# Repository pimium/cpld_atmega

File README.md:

# CPLD ATmega

An EDA Development Board to work with CPLD and ATmega

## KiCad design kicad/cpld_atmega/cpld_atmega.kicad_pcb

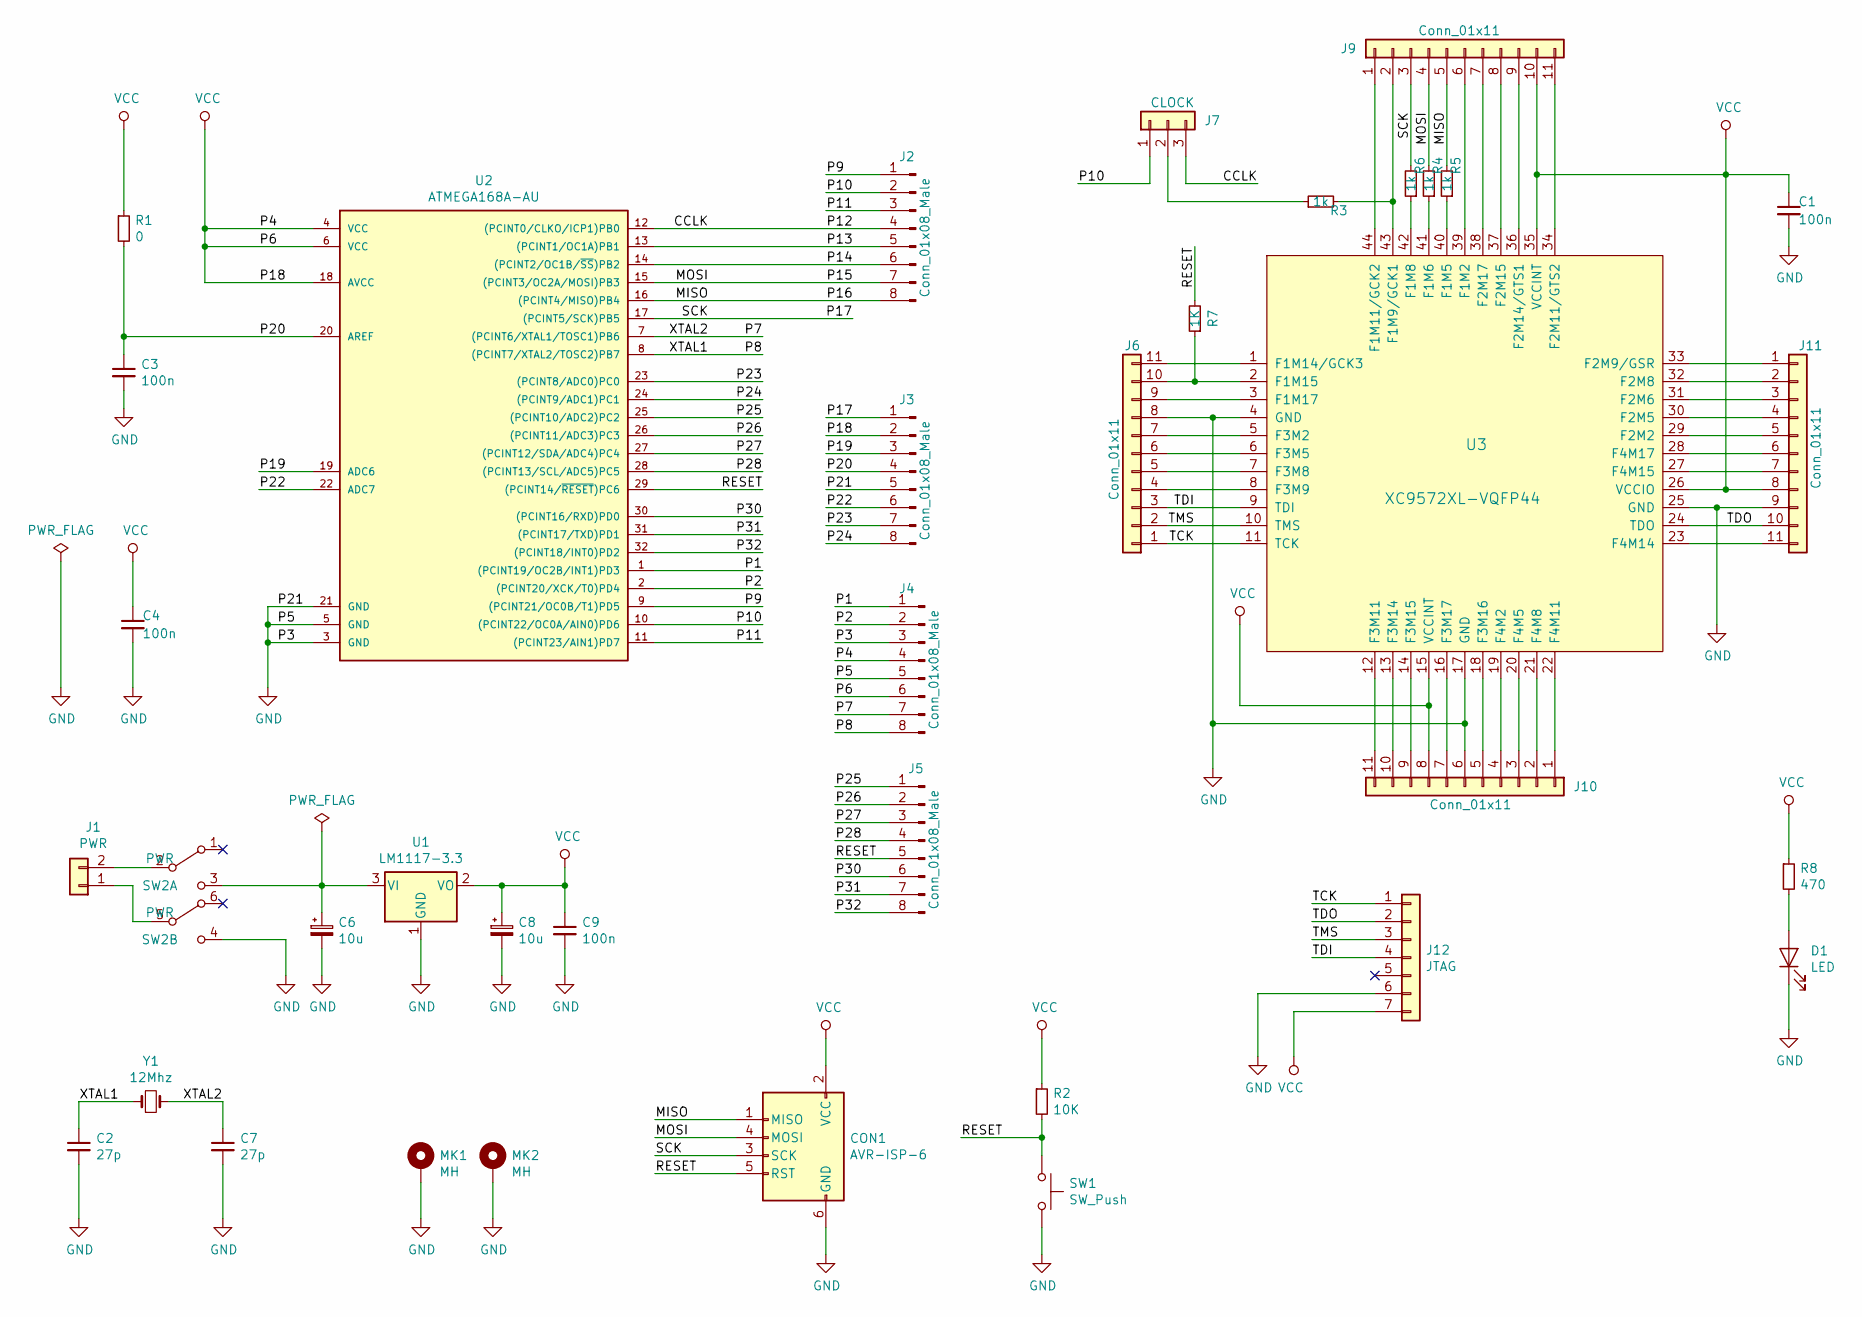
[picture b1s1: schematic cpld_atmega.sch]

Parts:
C1: 100n; C_0805_HandSoldering
C2, C7: 27p; C_0805_HandSoldering
C3, C4, C9: 100n; C_0805_2012Metric_Pad1.15x1.40mm_HandSolder
C6, C8: 10u; CP_Radial_D5.0mm_P2.50mm
CON1: AVR-ISP-6; Pin_Header_Straight_2x03_Pitch2.54mm
D1: LED; LED_1206_3216Metric_Pad1.42x1.75mm_HandSolder
J1: PWR; TerminalBlock_RND_205-00001_1x02_P5.00mm_Horizontal
J2, J3, J4, J5: Conn_01x08_Male; PinSocket_1x08_P2.54mm_Vertical
J6, J9, J10, J11: Conn_01x11; PinSocket_1x11_P2.54mm_Vertical
J7: CLOCK; PinSocket_1x03_P2.54mm_Vertical
J12: JTAG; PinSocket_1x07_P2.54mm_Vertical
MK1, MK2: MH; MountingHole_2.5mm_Pad
R1: 0; R_0805_2012Metric_Pad1.15x1.40mm_HandSolder
R2: 10K; R_0603_1608Metric_Pad1.05x0.95mm_HandSolder
R3, R4, R5, R6: 1k; R_0603_1608Metric_Pad1.05x0.95mm_HandSolder
R7: 1K; R_0603_1608Metric_Pad1.05x0.95mm_HandSolder
R8: 470; R_0603_1608Metric_Pad1.05x0.95mm_HandSolder
SW1: SW_Push; SW_PUSH_6mm
SW2: PWR; DPDT_WIDE_54_54
U1: LM1117-3.3; SOT-223-3_TabPin2
U2: ATMEGA168A-AU; TQFP-32_7x7mm_Pitch0.8mm
U3: XC9572XL-VQFP44; LQFP-44_10x10mm_P0.8mm
Y1: 12Mhz; Crystal_SMD_HC49-SD

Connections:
/CCLK: J2.4, J7.3, U2.12 ((PCINT0/CLKO/ICP1)PB0)
/MISO: CON1.1 (MISO), J2.8, J9.5, R5.2, U2.16 ((PCINT4/MISO)PB4)
/MOSI: CON1.4 (MOSI), J2.7, J9.4, R4.2, U2.15 ((PCINT3/OC2A/MOSI)PB3)
/P1: J4.1, U2.1 ((PCINT19/OC2B/INT1)PD3)
/P2: J4.2, U2.2 ((PCINT20/XCK/T0)PD4)
/P7: C7.1, J4.7, U2.7 ((PCINT6/XTAL1/TOSC1)PB6), Y1.2
/P8: C2.1, J4.8, U2.8 ((PCINT7/XTAL2/TOSC2)PB7), Y1.1
/P9: J2.1, U2.9 ((PCINT21/OC0B/T1)PD5)
/P10: J2.2, J7.1, U2.10 ((PCINT22/OC0A/AIN0)PD6)
/P11: J2.3, U2.11 ((PCINT23/AIN1)PD7)
/P13: J2.5, U2.13 ((PCINT1/OC1A)PB1)
/P14: J2.6, U2.14 ((PCINT2/OC1B/~SS~)PB2)
/P17: CON1.3 (SCK), J3.1, J9.3, R6.2, U2.17 ((PCINT5/SCK)PB5)
/P19: J3.3, U2.19 (ADC6)
/P20: C3.1, J3.4, R1.2, U2.20 (AREF)
/P22: J3.6, U2.22 (ADC7)
/P23: J3.7, U2.23 ((PCINT8/ADC0)PC0)
/P24: J3.8, U2.24 ((PCINT9/ADC1)PC1)
/P25: J5.1, U2.25 ((PCINT10/ADC2)PC2)
/P26: J5.2, U2.26 ((PCINT11/ADC3)PC3)
/P27: J5.3, U2.27 ((PCINT12/SDA/ADC4)PC4)
/P28: J5.4, U2.28 ((PCINT13/SCL/ADC5)PC5)
/P30: J5.6, U2.30 ((PCINT16/RXD)PD0)
/P31: J5.7, U2.31 ((PCINT17/TXD)PD1)
/P32: J5.8, U2.32 ((PCINT18/INT0)PD2)
/RESET: CON1.5 (RST), J5.5, R2.2, R7.2, SW1.1, U2.29 ((PCINT14/~RESET~)PC6)
/TCK: J6.1, J12.1, U3.11 (TCK)
/TDI: J6.3, J12.4, U3.9 (TDI)
/TDO: J11.10, J12.2, U3.24 (TDO)
/TMS: J6.2, J12.3, U3.10 (TMS)
GND: C1.2, C2.2, C3.2, C4.2, C6.2, C7.2, C8.2, C9.2, CON1.6 (GND), D1.1 (K), J3.5, J4.3, J4.5, J6.8, J10.6, J11.9, J12.6, MK1.1, MK2.1, SW1.2, SW2.4 (C), U1.1 (GND), U2.3 (GND), U2.5 (GND), U2.21 (GND), U3.4 (GND), U3.17 (GND), U3.25 (GND)
unnamed: C6.1, SW2.3 (C), U1.3 (VI)
unnamed: D1.2 (A), R8.2
unnamed: J1.1, SW2.5 (B)
unnamed: J1.2, SW2.2 (B)
unnamed: J6.4, U3.8 (F3M9)
unnamed: J6.5, U3.7 (F3M8)
unnamed: J6.6, U3.6 (F3M5)
unnamed: J6.7, U3.5 (F3M2)
unnamed: J6.9, U3.3 (F1M17)
unnamed: J6.10, R7.1, U3.2 (F1M15)
unnamed: J6.11, U3.1 (F1M14/GCK3)
unnamed: J7.2, R3.1
unnamed: J9.1, U3.44 (F1M11/GCK2)
unnamed: J9.2, R3.2, U3.43 (F1M9/GCK1)
unnamed: J9.6, U3.39 (F1M2)
unnamed: J9.7, U3.38 (F2M17)
unnamed: J9.8, U3.37 (F2M15)
unnamed: J9.9, U3.36 (F2M14/GTS1)
unnamed: J9.11, U3.34 (F2M11/GTS2)
unnamed: J10.1, U3.22 (F4M11)
unnamed: J10.2, U3.21 (F4M8)
unnamed: J10.3, U3.20 (F4M5)
unnamed: J10.4, U3.19 (F4M2)
unnamed: J10.5, U3.18 (F3M16)
unnamed: J10.7, U3.16 (F3M17)
unnamed: J10.9, U3.14 (F3M15)
unnamed: J10.10, U3.13 (F3M14)
unnamed: J10.11, U3.12 (F3M11)
unnamed: J11.1, U3.33 (F2M9/GSR)
unnamed: J11.2, U3.32 (F2M8)
unnamed: J11.3, U3.31 (F2M6)
unnamed: J11.4, U3.30 (F2M5)
unnamed: J11.5, U3.29 (F2M2)
unnamed: J11.6, U3.28 (F4M17)
unnamed: J11.7, U3.27 (F4M15)
unnamed: J11.11, U3.23 (F4M14)
unnamed: R4.1, U3.41 (F1M6)
unnamed: R5.1, U3.40 (F1M5)
unnamed: R6.1, U3.42 (F1M8)
VCC: C1.1, C4.1, C8.1, C9.1, CON1.2 (VCC), J3.2, J4.4, J4.6, J9.10, J10.8, J11.8, J12.7, R1.1, R2.1, R8.1, U1.2 (VO), U2.4 (VCC), U2.6 (VCC), U2.18 (AVCC), U3.15 (VCCINT), U3.26 (VCCIO), U3.35 (VCCINT)

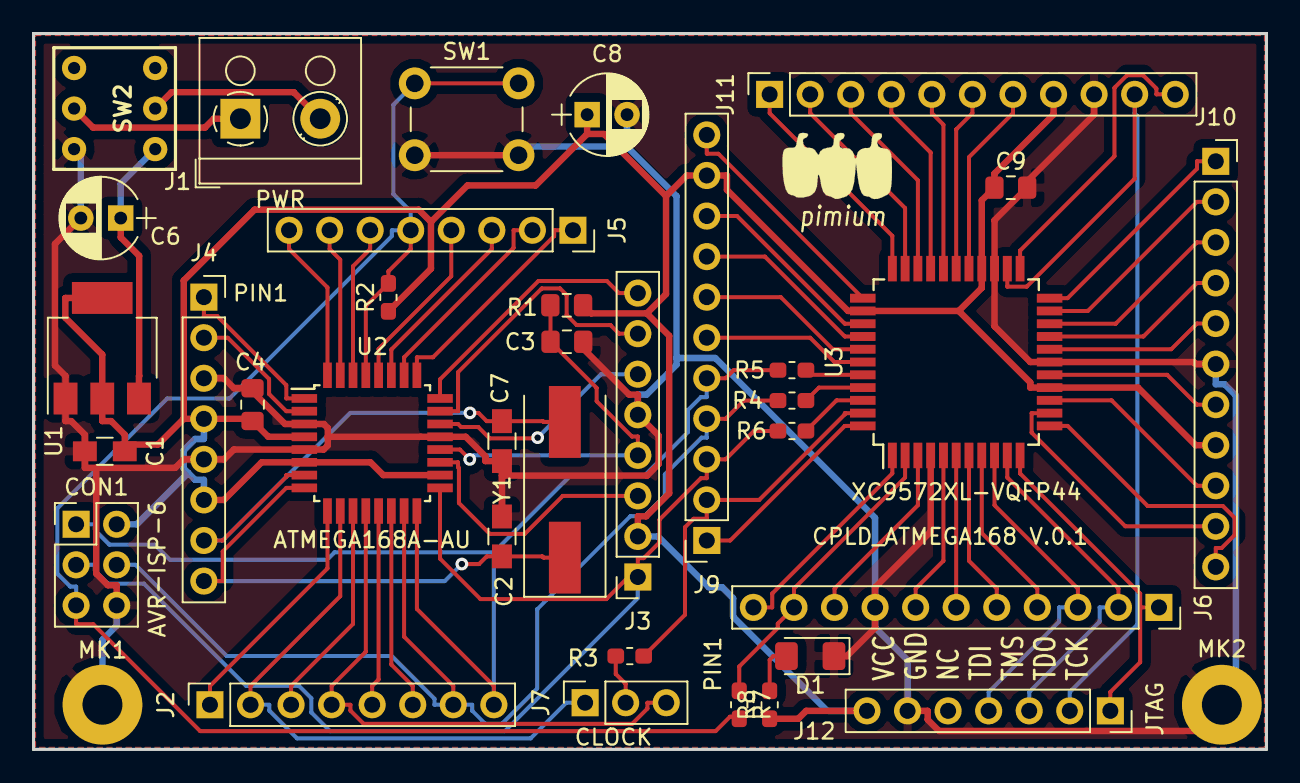
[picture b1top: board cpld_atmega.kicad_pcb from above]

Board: 2 copper layers, 77.2 x 44.8 mm, 37 parts (0 on the bottom side), 71 nets.

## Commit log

2018-01-20 zwischestand
2018-01-25 1.version almost done
2018-02-24 label s are added
2020-08-25 version 0.1
